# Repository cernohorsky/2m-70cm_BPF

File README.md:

# 2m-70cm_BPF
Highly selective 3-pole Chebyshev band-pass filter. Adjustable via capacitive trimmers. Can be built for both the 2m and 70cm bands.

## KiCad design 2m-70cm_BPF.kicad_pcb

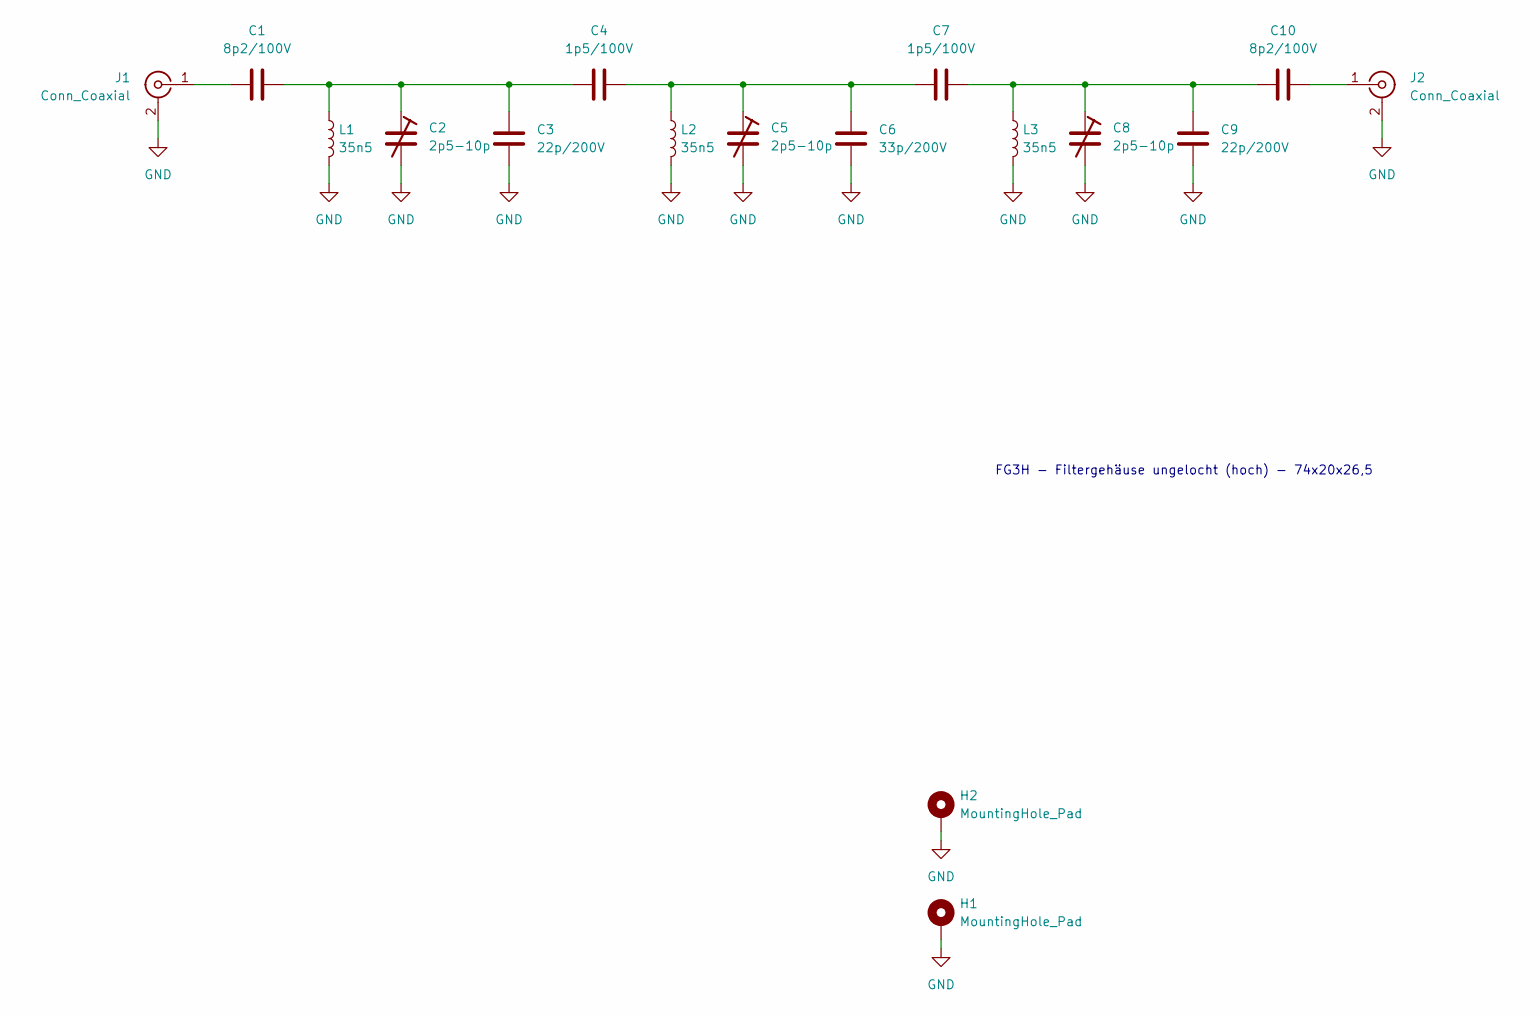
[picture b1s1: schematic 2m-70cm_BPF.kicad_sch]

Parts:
C1, C10: 8p2/100V; C_0805_2012Metric
C2, C5, C8: 2p5-10p; CERA-TRIM-SL
C3, C9: 22p/200V; C_0805_2012Metric
C4, C7: 1p5/100V; C_0805_2012Metric
C6: 33p/200V; C_0805_2012Metric
H1, H2: MountingHole_Pad; MountingHole_2.2mm_M2_Pad
J1, J2: Conn_Coaxial; SMA_Amphenol_132289_EdgeMount
L1, L2, L3: 35n5; L_Wurth_WE-CAIR-3168

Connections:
GND: C2.2, C3.1, C5.2, C6.1, C8.2, C9.1, H1.1, H2.1, J1.2 (Ext), J2.2 (Ext), L1.2, L2.2, L3.2
unnamed: C1.2, C2.1, C3.2, C4.1, L1.1
unnamed: C4.2, C5.1, C6.2, C7.1, L2.1
unnamed: C7.2, C8.1, C9.2, C10.2, L3.1
unnamed: C1.1, J1.1 (In)
unnamed: C10.1, J2.1 (In)

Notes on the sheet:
FG3H - Filtergehäuse ungelocht (hoch) - 74x20x26,5

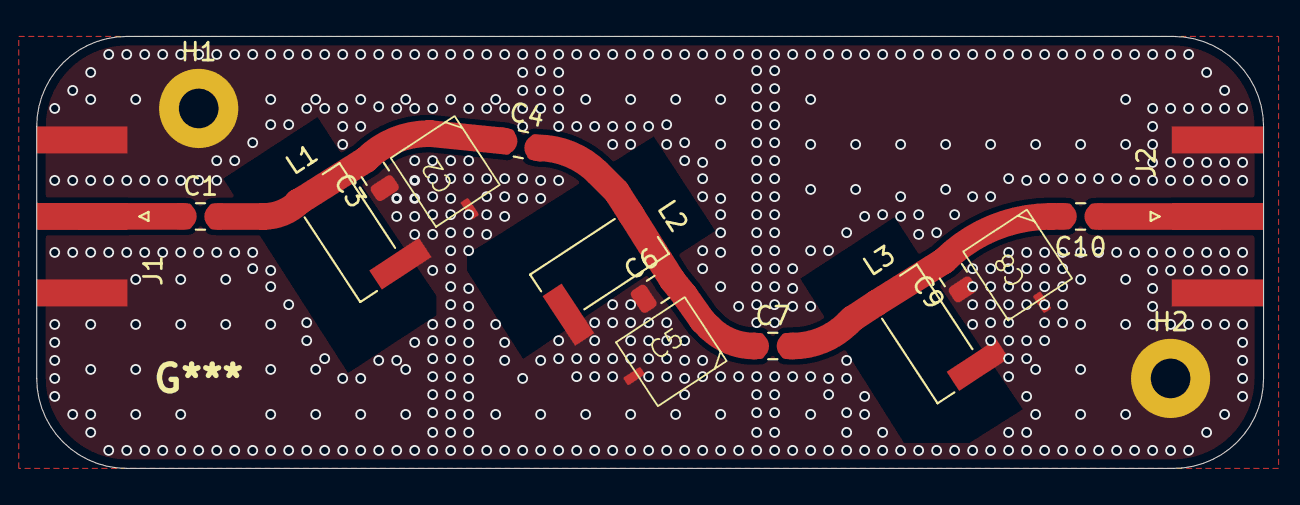
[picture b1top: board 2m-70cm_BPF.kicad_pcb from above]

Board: 2 copper layers, 68.2 x 24.0 mm, 17 parts (0 on the bottom side), 6 nets.

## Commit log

2026-02-26 Layout done. Checks pending
2026-02-26 Added QUCS simulation.
2026-02-26 Added components values for 70cm band..
2026-02-26 Update README.md - Schematic
2026-02-26 Added CERA-TRIM 3D model
2026-02-26 Added 137MHz NOAA option.
2026-02-26 Adjusted dividers masks.
2026-02-27 Inductors changes to 35n5. Better Q, 2m-137MHz combo.
